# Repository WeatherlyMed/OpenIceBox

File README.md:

# Open Ice Box
A from scratch remake of Ice Box keyboard with more options
A usb pcb only keyboard designed for silent switches and a foam backing

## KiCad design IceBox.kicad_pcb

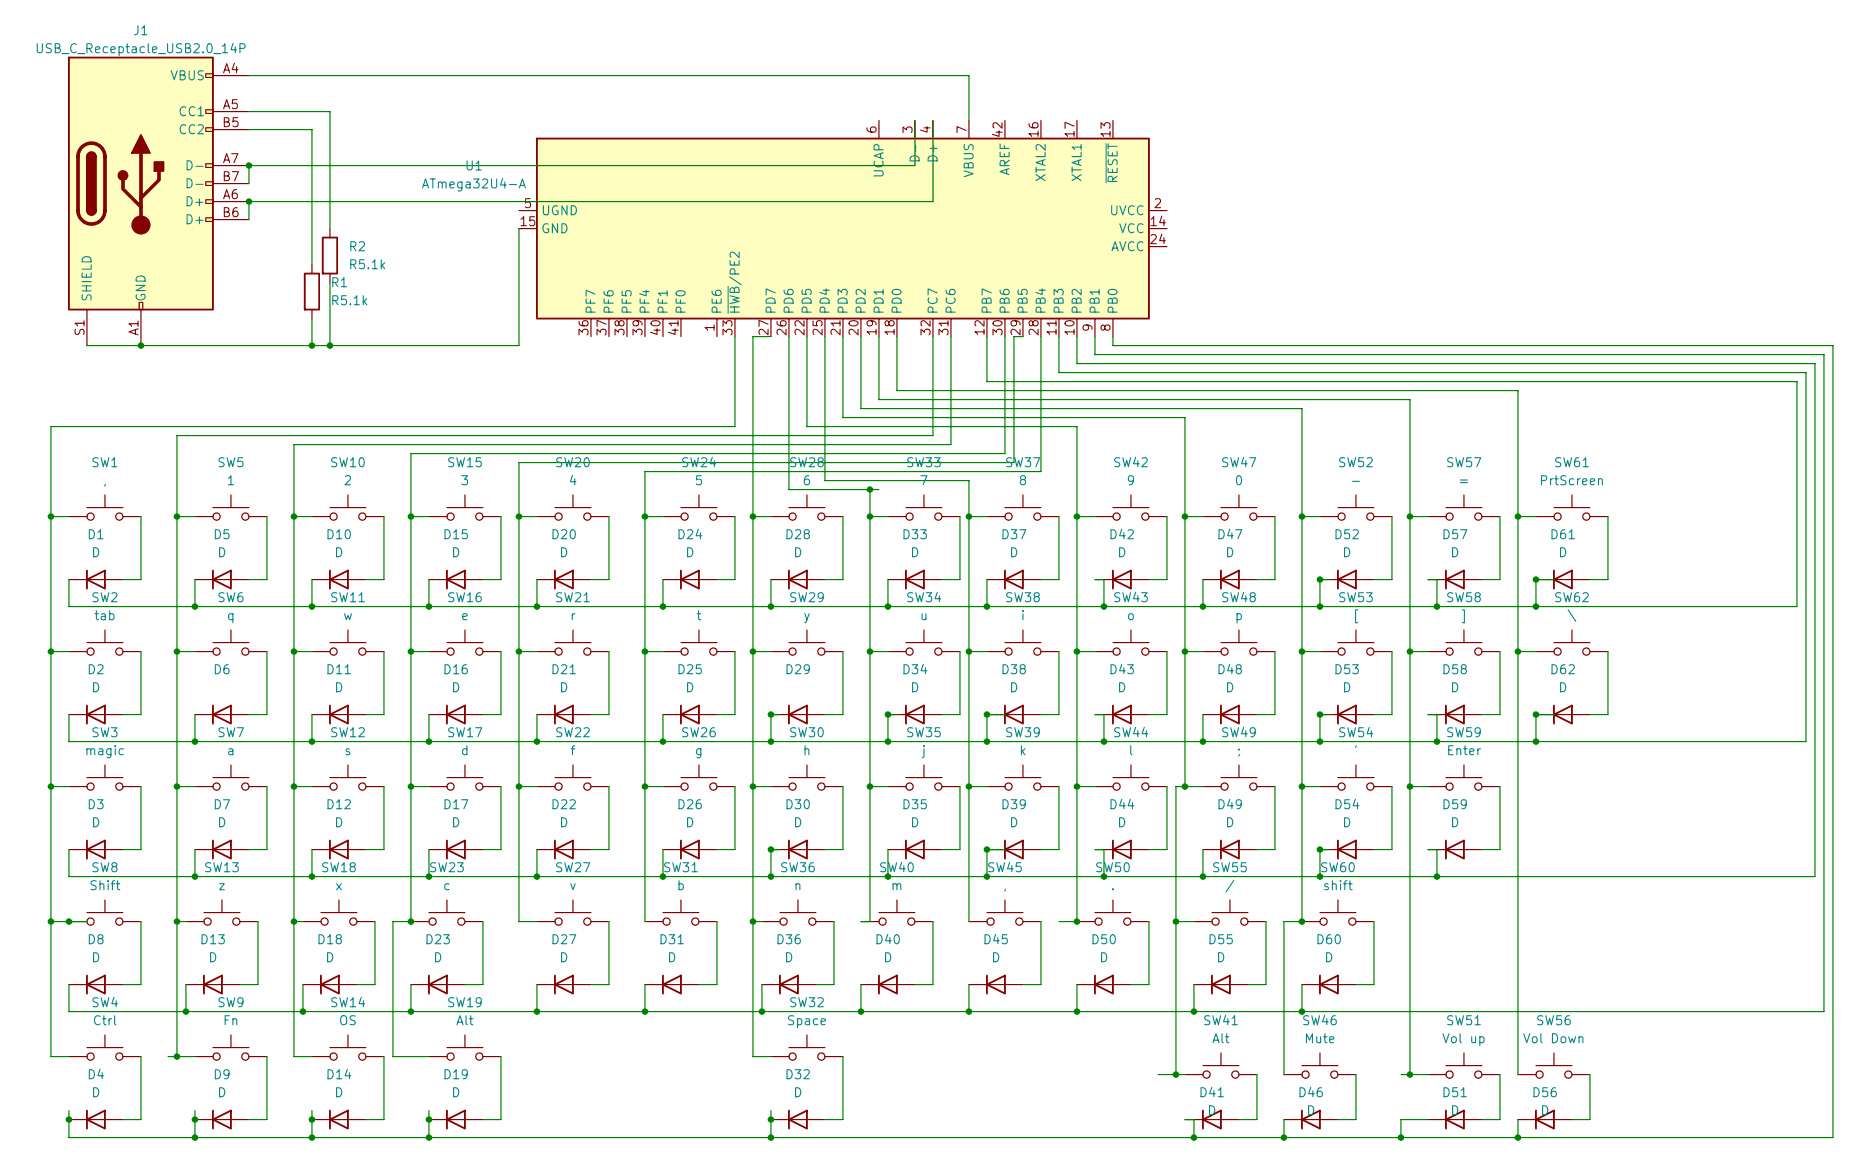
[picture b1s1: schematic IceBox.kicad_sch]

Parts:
D1, D2, D3, D4, D5, D6, D7, D8, D9, D10, D11, D12, D13, D14, D15, D16, D17, D18, D19, D20, D21, D22, D23, D24, D25, D26, D27, D28, D29, D30, D31, D32, D33, D34, D35, D36, D37, D38, D39, D40, D41, D42, D43, D44, D45, D46, D47, D48, D49, D50, D51, D52, D53, D54, D55, D56, D57, D58, D59, D60, D61, D62: D; D_SOD-123
J1: USB_C_Receptacle_USB2.0_14P; USB_C_Receptacle_GCT_USB4085
R1, R2: R5.1k; R_1206_3216Metric
SW1, SW45: ,; SW_Cherry_MX_1.00u_PCB
SW2: tab; SW_Cherry_MX_1.50u_PCB
SW3: magic; SW_Cherry_MX_1.75u_PCB
SW4: Ctrl; SW_Cherry_MX_1.25u_PCB
SW5: 1; SW_Cherry_MX_1.00u_PCB
SW6: q; SW_Cherry_MX_1.00u_PCB
SW7: a; SW_Cherry_MX_1.00u_PCB
SW8: Shift; SW_Cherry_MX_2.00u_PCB
SW9: Fn; SW_Cherry_MX_1.25u_PCB
SW10: 2; SW_Cherry_MX_1.00u_PCB
SW11: w; SW_Cherry_MX_1.00u_PCB
SW12: s; SW_Cherry_MX_1.00u_PCB
SW13: z; SW_Cherry_MX_1.00u_PCB
SW14: OS; SW_Cherry_MX_1.25u_PCB
SW15: 3; SW_Cherry_MX_1.00u_PCB
SW16: e; SW_Cherry_MX_1.00u_PCB
SW17: d; SW_Cherry_MX_1.00u_PCB
SW18: x; SW_Cherry_MX_1.00u_PCB
SW19: Alt; SW_Cherry_MX_1.00u_PCB
SW20: 4; SW_Cherry_MX_1.00u_PCB
SW21: r; SW_Cherry_MX_1.00u_PCB
SW22: f; SW_Cherry_MX_1.00u_PCB
SW23: c; SW_Cherry_MX_1.00u_PCB
SW24: 5; SW_Cherry_MX_1.00u_PCB
SW25: t; SW_Cherry_MX_1.00u_PCB
SW26: g; SW_Cherry_MX_1.00u_PCB
SW27: v; SW_Cherry_MX_1.00u_PCB
SW28: 6; SW_Cherry_MX_1.00u_PCB
SW29: y; SW_Cherry_MX_1.00u_PCB
SW30: h; SW_Cherry_MX_1.00u_PCB
SW31: b; SW_Cherry_MX_1.00u_PCB
SW32: Space; SW_Cherry_MX_6.25u_PCB
SW33: 7; SW_Cherry_MX_1.00u_PCB
SW34: u; SW_Cherry_MX_1.00u_PCB
SW35: j; SW_Cherry_MX_1.00u_PCB
SW36: n; SW_Cherry_MX_1.00u_PCB
SW37: 8; SW_Cherry_MX_1.00u_PCB
SW38: i; SW_Cherry_MX_1.00u_PCB
SW39: k; SW_Cherry_MX_1.00u_PCB
SW40: m; SW_Cherry_MX_1.00u_PCB
SW41: Alt; SW_Cherry_MX_1.25u_PCB
SW42: 9; SW_Cherry_MX_1.00u_PCB
SW43: o; SW_Cherry_MX_1.00u_PCB
SW44: l; SW_Cherry_MX_1.00u_PCB
SW46: Mute; SW_Cherry_MX_1.25u_PCB
SW47: 0; SW_Cherry_MX_1.00u_PCB
SW48: p; SW_Cherry_MX_1.00u_PCB
SW49: ;; SW_Cherry_MX_1.00u_PCB
SW50: .; SW_Cherry_MX_1.00u_PCB
SW51: Vol up; SW_Cherry_MX_1.25u_PCB
SW52: -; SW_Cherry_MX_1.00u_PCB
SW53: [; SW_Cherry_MX_1.00u_PCB
SW54: '; SW_Cherry_MX_1.00u_PCB
SW55: /; SW_Cherry_MX_1.00u_PCB
SW56: Vol Down; SW_Cherry_MX_1.25u_PCB
SW57: =; SW_Cherry_MX_1.00u_PCB
SW58: ]; SW_Cherry_MX_1.00u_PCB
SW59: Enter; SW_Cherry_MX_2.00u_PCB
SW60: shift; SW_Cherry_MX_2.25u_PCB
SW61: PrtScreen; SW_Cherry_MX_1.00u_PCB
SW62: \; SW_Cherry_MX_1.75u_PCB
U1: ATmega32U4-A; TQFP-44_10x10mm_P0.8mm

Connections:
unnamed: D1.2 (A), SW1.2
unnamed: D2.2 (A), SW2.2
unnamed: D3.2 (A), SW3.2
unnamed: D4.2 (A), SW4.2
unnamed: D5.2 (A), SW5.2
unnamed: D6.2 (A), SW6.2
unnamed: D7.2 (A), SW7.2
unnamed: D8.2 (A), SW8.2
unnamed: D9.2 (A), SW9.2
unnamed: D10.2 (A), SW10.2
unnamed: D11.2 (A), SW11.2
unnamed: D12.2 (A), SW12.2
unnamed: D3.1 (K), D7.1 (K), D12.1 (K), D17.1 (K), D22.1 (K), D26.1 (K), D30.1 (K), D35.1 (K), D39.1 (K), D44.1 (K), D49.1 (K), D54.1 (K), D59.1 (K), U1.10 (PB2)
unnamed: D13.2 (A), SW13.2
unnamed: D14.2 (A), SW14.2
unnamed: D15.2 (A), SW15.2
unnamed: D16.2 (A), SW16.2
unnamed: D17.2 (A), SW17.2
unnamed: D18.2 (A), SW18.2
unnamed: D19.2 (A), SW19.2
unnamed: D20.2 (A), SW20.2
unnamed: D21.2 (A), SW21.2
unnamed: D22.2 (A), SW22.2
unnamed: D23.2 (A), SW23.2
unnamed: D24.2 (A), SW24.2
unnamed: D25.2 (A), SW25.2
unnamed: D26.2 (A), SW26.2
unnamed: D27.2 (A), SW27.2
unnamed: D28.2 (A), SW28.2
unnamed: D29.2 (A), SW29.2
unnamed: D30.2 (A), SW30.2
unnamed: D31.2 (A), SW31.2
unnamed: D32.2 (A), SW32.2
unnamed: D33.2 (A), SW33.2
unnamed: D34.2 (A), SW34.2
unnamed: D35.2 (A), SW35.2
unnamed: D36.2 (A), SW36.2
unnamed: D37.2 (A), SW37.2
unnamed: D38.2 (A), SW38.2
unnamed: D39.2 (A), SW39.2
unnamed: D40.2 (A), SW40.2
unnamed: D41.2 (A), SW41.2
unnamed: D42.2 (A), SW42.2
unnamed: D43.2 (A), SW43.2
unnamed: D44.2 (A), SW44.2
unnamed: D45.2 (A), SW45.2
unnamed: D46.2 (A), SW46.2
unnamed: D47.2 (A), SW47.2
unnamed: D48.2 (A), SW48.2
unnamed: D49.2 (A), SW49.2
unnamed: D50.2 (A), SW50.2
unnamed: D51.2 (A), SW51.2
unnamed: D52.2 (A), SW52.2
unnamed: D53.2 (A), SW53.2
unnamed: D54.2 (A), SW54.2
unnamed: D55.2 (A), SW55.2
unnamed: D56.2 (A), SW56.2
unnamed: D57.2 (A), SW57.2
unnamed: D58.2 (A), SW58.2
unnamed: D59.2 (A), SW59.2
unnamed: D60.2 (A), SW60.2
unnamed: D61.2 (A), SW61.2
unnamed: D62.2 (A), SW62.2
unnamed: J1.A5 (CC1), R2.1
unnamed: J1.B5 (CC2), R1.1
unnamed: J1.A1 (GND), J1.A12 (GND), J1.B1 (GND), J1.B12 (GND), J1.S1 (SHIELD), R1.2, R2.2, U1.15 (GND), U1.23 (GND), U1.35 (GND), U1.43 (GND)
unnamed: U1.24 (AVCC), U1.44 (AVCC)
unnamed: J1.A6 (D+), J1.B6 (D+), U1.4 (D+)
unnamed: J1.A7 (D-), J1.B7 (D-), U1.3 (D-)
unnamed: SW24.1, SW25.1, SW26.1, SW31.1, U1.28 (PB4)
unnamed: SW20.1, SW21.1, SW22.1, SW27.1, U1.29 (PB5)
unnamed: SW15.1, SW16.1, SW17.1, SW19.1, SW23.1, U1.30 (PB6)
unnamed: SW10.1, SW11.1, SW12.1, SW14.1, SW18.1, U1.31 (PC6)
unnamed: SW5.1, SW6.1, SW7.1, SW9.1, SW13.1, U1.32 (PC7)
unnamed: SW56.1, SW61.1, SW62.1, U1.18 (PD0)
unnamed: SW51.1, SW57.1, SW58.1, SW59.1, U1.19 (PD1)
unnamed: SW46.1, SW52.1, SW53.1, SW54.1, SW60.1, U1.20 (PD2)
unnamed: SW41.1, SW47.1, SW48.1, SW49.1, SW55.1, U1.21 (PD3)
unnamed: SW37.1, SW38.1, SW39.1, SW45.1, U1.25 (PD4)
unnamed: SW42.1, SW43.1, SW44.1, SW50.1, U1.22 (PD5)
unnamed: SW33.1, SW34.1, SW35.1, SW40.1, U1.26 (PD6)
unnamed: SW28.1, SW29.1, SW30.1, SW32.1, SW36.1, U1.27 (PD7)
unnamed: J1.A4 (VBUS), J1.A9 (VBUS), J1.B4 (VBUS), J1.B9 (VBUS), U1.7 (VBUS)
unnamed: U1.14 (VCC), U1.34 (VCC)
unnamed: SW1.1, SW2.1, SW3.1, SW4.1, SW8.1, U1.33 (~HWB/PE2)

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
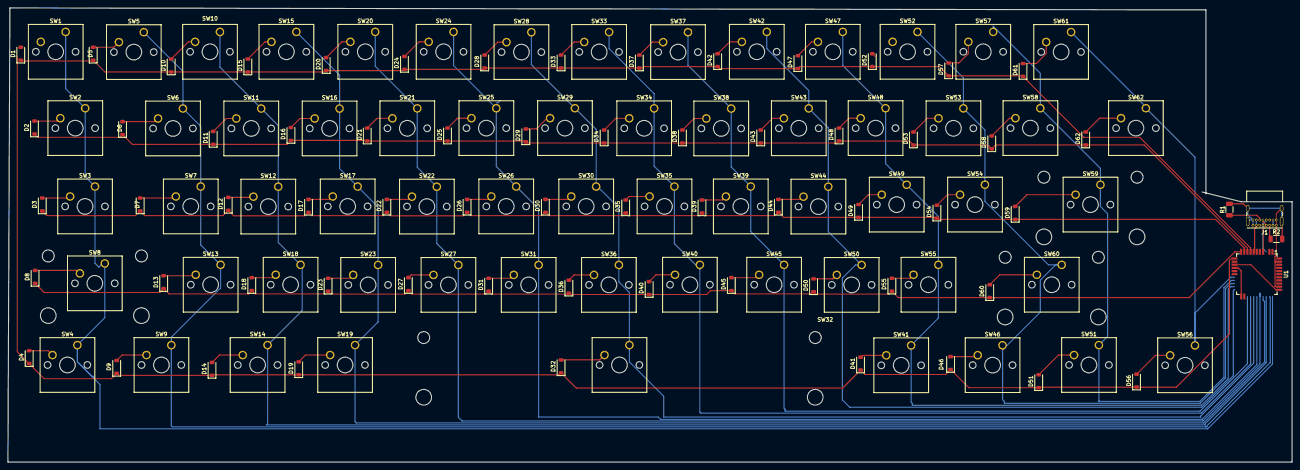
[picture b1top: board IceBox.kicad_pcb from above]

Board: 2 copper layers, 328.0 x 116.0 mm, 128 parts (0 on the bottom side), 89 nets.

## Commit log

2024-08-30 Add files via upload
    lots of research and a little sketch
    https://www.reddit.com/r/PrintedCircuitBoard/comments/kvat9d/usb_type_c_with_atmega32u4/
    https://www.digikey.com/en/products/detail/gct/USB4110-GF-A/10384547
